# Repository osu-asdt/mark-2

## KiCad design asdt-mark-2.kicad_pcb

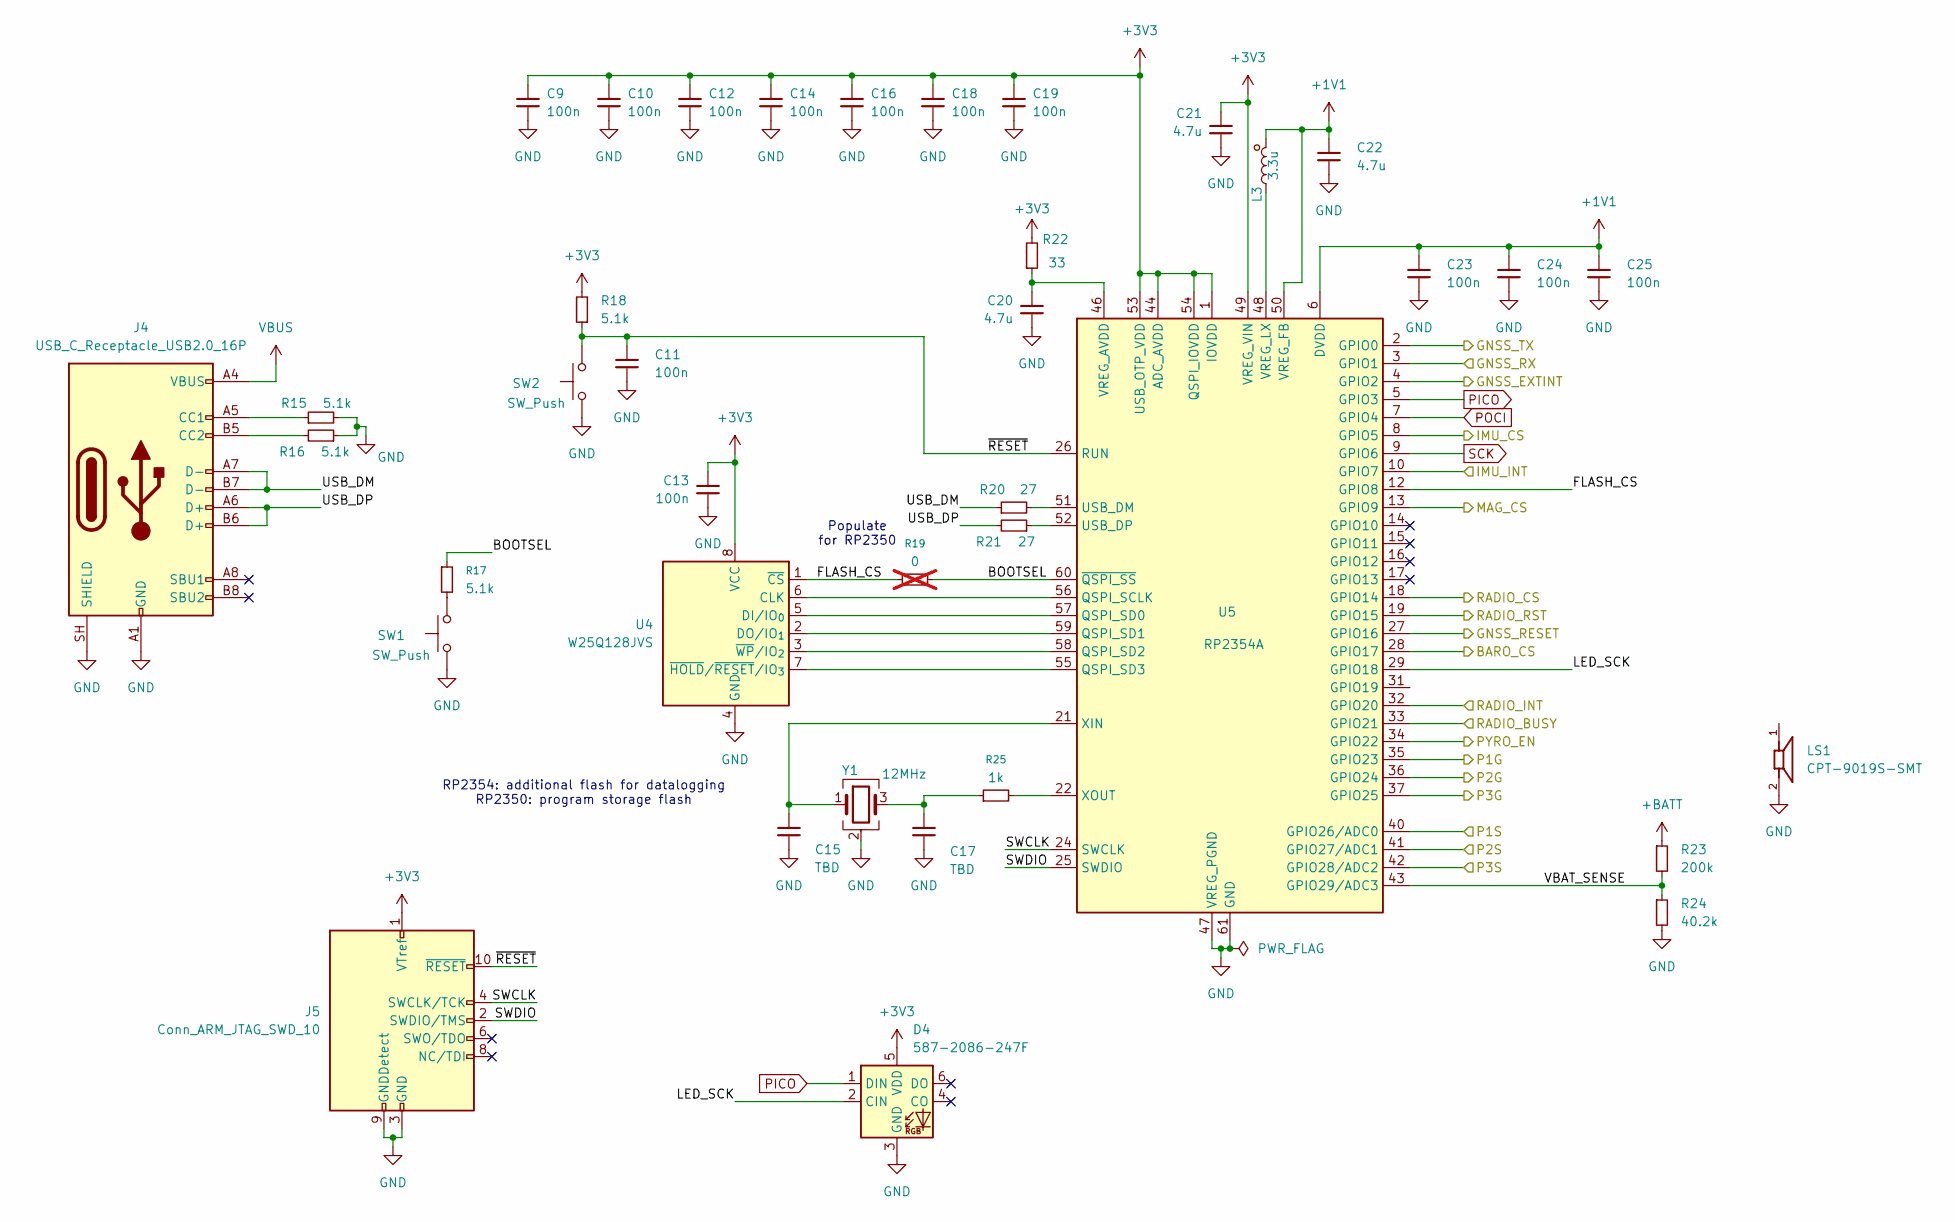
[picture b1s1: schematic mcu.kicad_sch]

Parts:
C9, C10, C12, C13, C14, C16, C18, C19: 100n; C_0201_0603Metric
C11: 100n; C_0201_0603Metric; Voltage 6.3V
C15, C17: TBD; C_0201_0603Metric
C20: 4.7u; C_0402_1005Metric
C21, C22: 4.7u; C_0402_1005Metric; Voltage 10V
C23, C24, C25: 100n; C_0201_0603Metric; Voltage 16V
D4: 587-2086-247F; LED-587-2086-247F-3228
J4: USB_C_Receptacle_USB2.0_16P; USB_C_Receptacle_GCT_USB4105-xx-A_16P_TopMnt_Horizontal
J5: Conn_ARM_JTAG_SWD_10; PinHeader_2x05_P1.27mm_Vertical_SMD
L3: 3.3u; L_0806_2016Metric
LS1: CPT-9019S-SMT; CUI_CPT-9019S-SMT; MPN CPT-9019S-SMT-TR
R15, R16, R17, R18: 5.1k; R_0201_0603Metric
R19: 0; R_0201_0603Metric; not fitted
R20, R21: 27; R_0201_0603Metric
R22: 33; R_0201_0603Metric
R23: 200k; R_0201_0603Metric
R24: 40.2k; R_0201_0603Metric
R25: 1k; R_0201_0603Metric
SW1, SW2: SW_Push; SW_SPST_PTS810
U4: W25Q128JVS; SOIC-8_5.3x5.3mm_P1.27mm
U5: RP2354A; QFN-60-1EP_7x7mm_P0.4mm_EP3.4x3.4mm
Y1: 12MHz; Crystal_SMD_Abracon_ABM8G-4Pin_3.2x2.5mm

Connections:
+1V1: C22.1, C23.1, C24.1, C25.1, L3.1, U5.6 (DVDD), U5.23 (DVDD), U5.39 (DVDD), U5.50 (VREG_FB)
+3V3: C9.1, C10.1, C12.1, C13.1, C14.1, C16.1, C18.1, C19.1, C21.1, D4.5 (VDD), J5.1 (VTref), R18.2, R22.2, U4.8 (VCC), U5.1 (IOVDD), U5.11 (IOVDD), U5.20 (IOVDD), U5.30 (IOVDD), U5.38 (IOVDD), U5.44 (ADC_AVDD), U5.45 (IOVDD), U5.49 (VREG_VIN), U5.53 (USB_OTP_VDD), U5.54 (QSPI_IOVDD); also elsewhere on the board
+BATT: R23.1; also elsewhere on the board
/MCU/BARO_CS: U5.28 (GPIO17)
/MCU/BOOTSEL: R17.1, R19.2, U5.60 (~QSPI_SS)
/MCU/FLASH_CS: R19.1, U4.1 (~CS), U5.12 (GPIO8)
/MCU/GNSS_EXTINT: U5.4 (GPIO2); also elsewhere on the board
/MCU/GNSS_RESET: U5.27 (GPIO16); also elsewhere on the board
/MCU/GNSS_RX: U5.3 (GPIO1); also elsewhere on the board
/MCU/GNSS_TX: U5.2 (GPIO0); also elsewhere on the board
/MCU/IMU_CS: U5.8 (GPIO5); also elsewhere on the board
/MCU/IMU_INT: U5.10 (GPIO7); also elsewhere on the board
/MCU/LED_SCK: D4.2 (CIN), U5.29 (GPIO18)
/MCU/MAG_CS: U5.13 (GPIO9); also elsewhere on the board
/MCU/P1G: U5.35 (GPIO23); also elsewhere on the board
/MCU/P1S: U5.40 (GPIO26/ADC0); also elsewhere on the board
/MCU/P2G: U5.36 (GPIO24); also elsewhere on the board
/MCU/P2S: U5.41 (GPIO27/ADC1); also elsewhere on the board
/MCU/P3G: U5.37 (GPIO25); also elsewhere on the board
/MCU/P3S: U5.42 (GPIO28/ADC2); also elsewhere on the board
/MCU/PYRO_EN: U5.34 (GPIO22); also elsewhere on the board
/MCU/RADIO_BUSY: U5.33 (GPIO21); also elsewhere on the board
/MCU/RADIO_CS: U5.18 (GPIO14); also elsewhere on the board
/MCU/RADIO_INT: U5.32 (GPIO20); also elsewhere on the board
/MCU/RADIO_RST: U5.19 (GPIO15); also elsewhere on the board
/MCU/SWCLK: J5.4 (SWCLK/TCK), U5.24 (SWCLK)
/MCU/SWDIO: J5.2 (SWDIO/TMS), U5.25 (SWDIO)
/MCU/USB_DM: J4.A7 (D-), J4.B7 (D-), R20.1
/MCU/USB_DP: J4.A6 (D+), J4.B6 (D+), R21.2
/MCU/VBAT_SENSE: R23.2, R24.1, U5.43 (GPIO29/ADC3)
/MCU/~RESET: C11.1, J5.10 (~RESET), R18.1, SW2.2, U5.26 (RUN)
GND: C9.2, C10.2, C11.2, C12.2, C13.2, C14.2, C15.2, C16.2, C17.2, C18.2, C19.2, C20.2, C21.2, C22.2, C23.2, C24.2, C25.2, D4.3 (GND), J4.A1 (GND), J4.A12 (GND), J4.B1 (GND), J4.B12 (GND), J4.SH (SHIELD), J5.3 (GND), J5.5 (GND), J5.9 (GNDDetect), R15.2, R16.1, R24.2, SW1.1, SW2.1, U4.4 (GND), U5.47 (VREG_PGND), U5.61 (GND), Y1.2 (G), Y1.4 (G); also elsewhere on the board
unnamed: C17.1, R25.1, Y1.3
unnamed: J4.A5 (CC1), R15.1
unnamed: J4.B5 (CC2), R16.2
unnamed: R17.2, SW1.2
unnamed: U4.6 (CLK), U5.56 (QSPI_SCLK)
unnamed: U4.5 (DI/IO_{0}), U5.57 (QSPI_SD0)
unnamed: U4.2 (DO/IO_{1}), U5.59 (QSPI_SD1)
unnamed: U4.7 (~HOLD/~RESET/IO_{3}), U5.55 (QSPI_SD3)
unnamed: U4.3 (~WP/IO_{2}), U5.58 (QSPI_SD2)
unnamed: R20.2, U5.51 (USB_DM)
unnamed: R21.1, U5.52 (USB_DP)
unnamed: C20.1, R22.1, U5.46 (VREG_AVDD)
unnamed: L3.2, U5.48 (VREG_LX)
unnamed: C15.1, U5.21 (XIN), Y1.1
unnamed: R25.2, U5.22 (XOUT)
PICO: D4.1 (DIN), U5.5 (GPIO3); also elsewhere on the board
POCI: U5.7 (GPIO4); also elsewhere on the board
SCK: U5.9 (GPIO6); also elsewhere on the board
VBUS: J4.A4 (VBUS), J4.A9 (VBUS), J4.B4 (VBUS), J4.B9 (VBUS); also elsewhere on the board

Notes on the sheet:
Populate for RP2350
RP2354: additional flash for datalogging RP2350: program storage flash

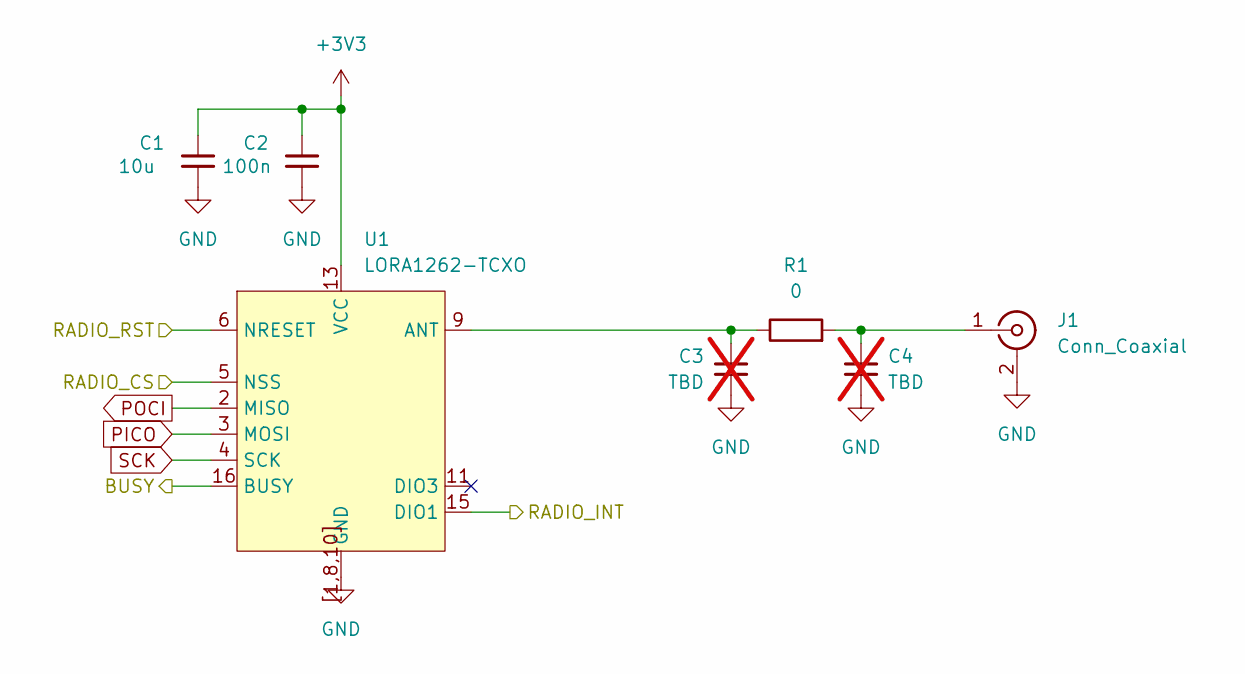
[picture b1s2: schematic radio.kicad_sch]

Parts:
C1: 10u; R_0603_1608Metric
C2: 100n; C_0201_0603Metric
C3, C4: TBD; C_0201_0603Metric; not fitted
J1: Conn_Coaxial; SMA_Samtec_SMA-J-P-H-ST-EM1_EdgeMount
R1: 0; R_0201_0603Metric
U1: LORA1262-TCXO; NiceRF-LORA126x

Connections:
+3V3: C1.1, C2.1, U1.13 (VCC); also elsewhere on the board
/MCU/RADIO_BUSY: U1.16 (BUSY); also elsewhere on the board
/MCU/RADIO_CS: U1.5 (NSS); also elsewhere on the board
/MCU/RADIO_INT: U1.15 (DIO1); also elsewhere on the board
/MCU/RADIO_RST: U1.6 (NRESET); also elsewhere on the board
GND: C1.2, C2.2, C3.2, C4.2, J1.2 (Ext), U1.[1,8,10] (GND); also elsewhere on the board
unnamed: C4.1, J1.1 (In), R1.2
unnamed: C3.1, R1.1, U1.9 (ANT)
PICO: U1.3 (MOSI); also elsewhere on the board
POCI: U1.2 (MISO); also elsewhere on the board
SCK: U1.4 (SCK); also elsewhere on the board

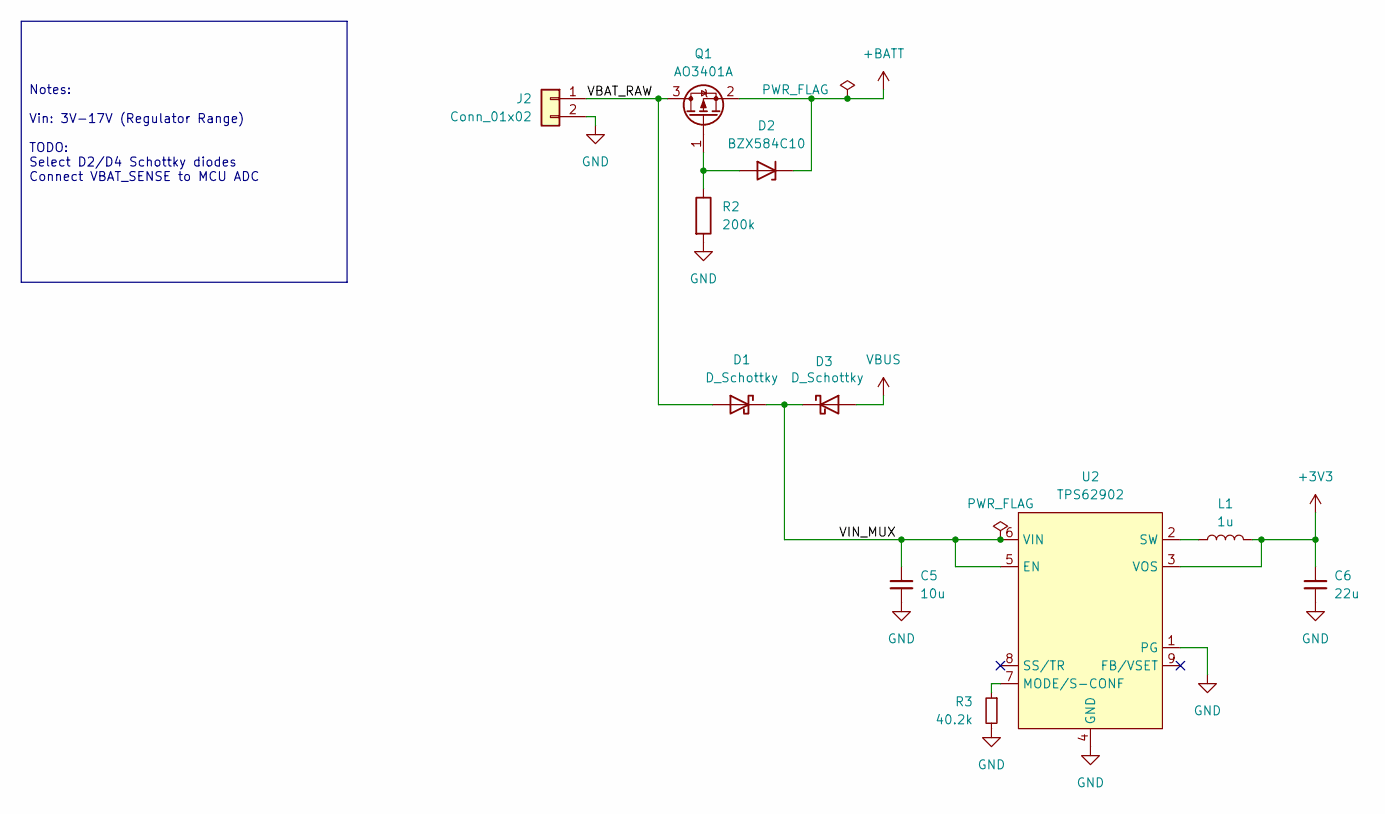
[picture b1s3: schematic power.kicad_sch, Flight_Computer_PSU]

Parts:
C5: 10u; R_0603_1608Metric
C6: 22u; R_0402_1005Metric
D1, D3: D_Schottky; D_SOD-123
D2: BZX584C10; D_SOD-523; LCSC Part# C22395577
J2: Conn_01x02; TerminalBlock_Xinya_XY308-2.54-2P_1x02_P2.54mm_Horizontal
L1: 1u; L_1008_2520Metric
Q1: AO3401A; SOT-23
R2: 200k; R_0201_0603Metric
R3: 40.2k; R_0201_0603Metric
U2: TPS62902; Texas_RPJ0009A_VQFN-HR-9_1.5x2mm_P0.5mm

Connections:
+3V3: C6.1, L1.2, U2.3 (VOS); also elsewhere on the board
+BATT: D2.1 (K), Q1.2 (S); also elsewhere on the board
/Power/VBAT_RAW: D1.2 (A), J2.1, Q1.3 (D)
/Power/VIN_MUX: C5.1, D1.1 (K), D3.1 (K), U2.5 (EN), U2.6 (VIN)
GND: C5.2, C6.2, J2.2, R2.2, R3.2, U2.1 (PG), U2.4 (GND); also elsewhere on the board
unnamed: D2.2 (A), Q1.1 (G), R2.1
unnamed: R3.1, U2.7 (MODE/S-CONF)
unnamed: L1.1, U2.2 (SW)
VBUS: D3.2 (A); also elsewhere on the board

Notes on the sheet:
Notes: Vin: 3V-17V (Regulator Range) TODO: Select D2/D4 Schottky diodes Connect VBAT_SENSE to MCU ADC

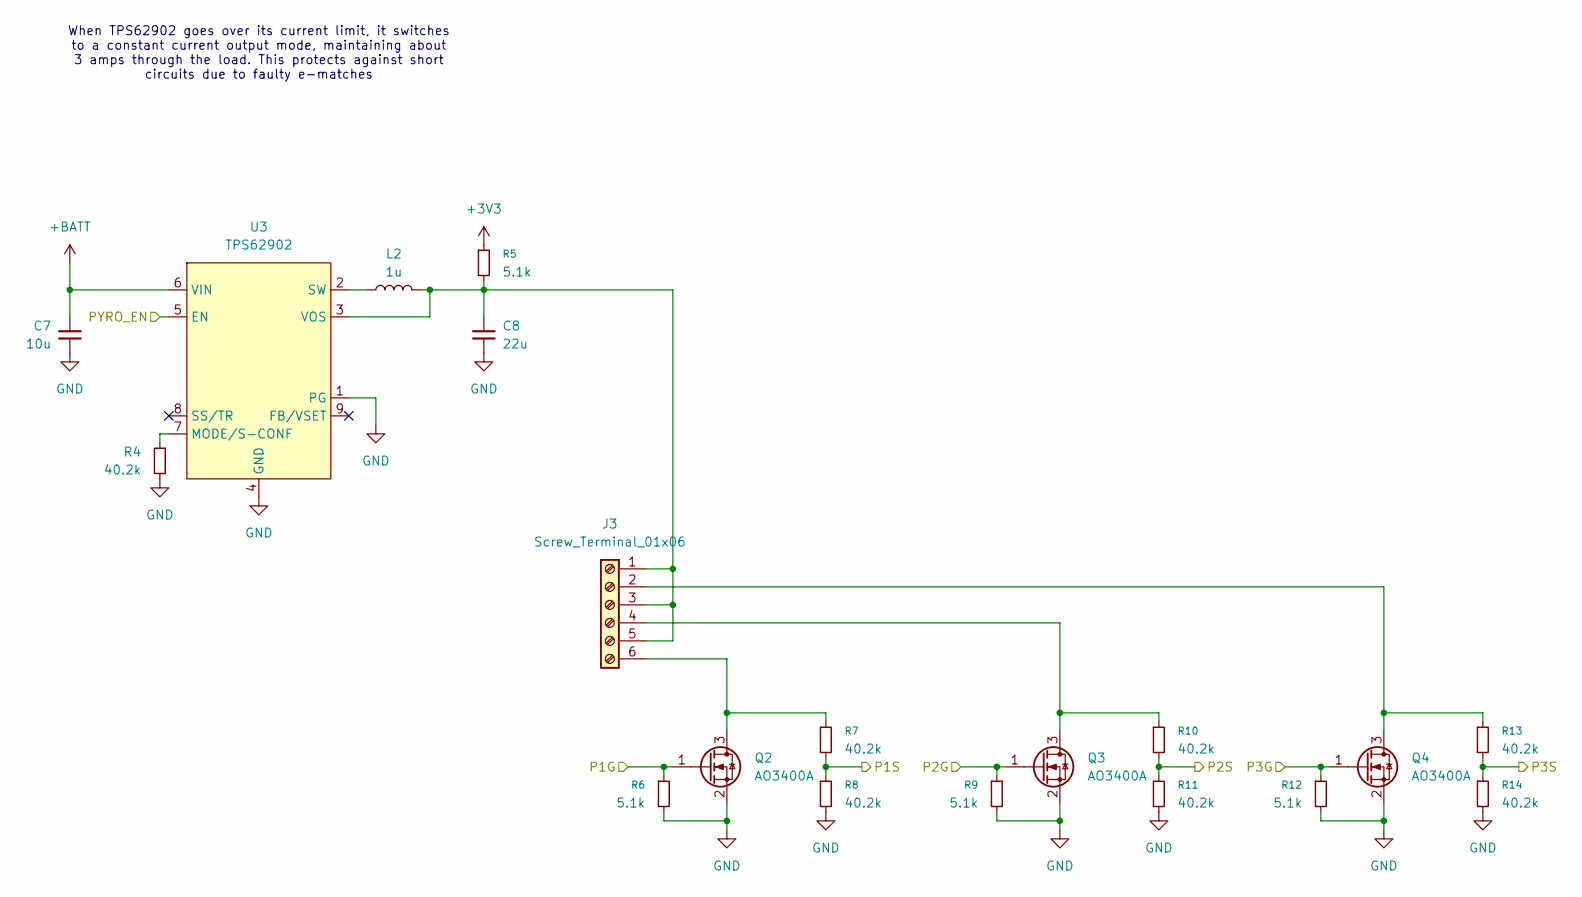
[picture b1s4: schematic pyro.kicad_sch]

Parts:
C7: 10u; R_0603_1608Metric
C8: 22u; R_0402_1005Metric
J3: Screw_Terminal_01x06; TerminalBlock_Xinya_XY308-2.54-6P_1x06_P2.54mm_Horizontal
L2: 1u; L_1008_2520Metric
Q2, Q3, Q4: AO3400A; SOT-23
R4, R7, R8, R10, R11, R13, R14: 40.2k; R_0201_0603Metric
R5, R6, R9, R12: 5.1k; R_0201_0603Metric
U3: TPS62902; Texas_RPJ0009A_VQFN-HR-9_1.5x2mm_P0.5mm

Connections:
+3V3: R5.1; also elsewhere on the board
+BATT: C7.1, U3.6 (VIN); also elsewhere on the board
/MCU/P1G: Q2.1 (G), R6.1; also elsewhere on the board
/MCU/P1S: R7.2, R8.1; also elsewhere on the board
/MCU/P2G: Q3.1 (G), R9.1; also elsewhere on the board
/MCU/P2S: R10.2, R11.1; also elsewhere on the board
/MCU/P3G: Q4.1 (G), R12.1; also elsewhere on the board
/MCU/P3S: R13.2, R14.1; also elsewhere on the board
/MCU/PYRO_EN: U3.5 (EN); also elsewhere on the board
GND: C7.2, C8.2, Q2.2 (S), Q3.2 (S), Q4.2 (S), R4.2, R6.2, R8.2, R9.2, R11.2, R12.2, R14.2, U3.1 (PG), U3.4 (GND); also elsewhere on the board
unnamed: C8.1, J3.1, J3.3, J3.5, L2.2, R5.2, U3.3 (VOS)
unnamed: J3.2, Q4.3 (D), R13.1
unnamed: J3.4, Q3.3 (D), R10.1
unnamed: J3.6, Q2.3 (D), R7.1
unnamed: R4.1, U3.7 (MODE/S-CONF)
unnamed: L2.1, U3.2 (SW)

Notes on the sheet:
When TPS62902 goes over its current limit, it switches to a constant current output mode, maintaining about 3 amps through the load. This protects against short circuits due to faulty e-matches

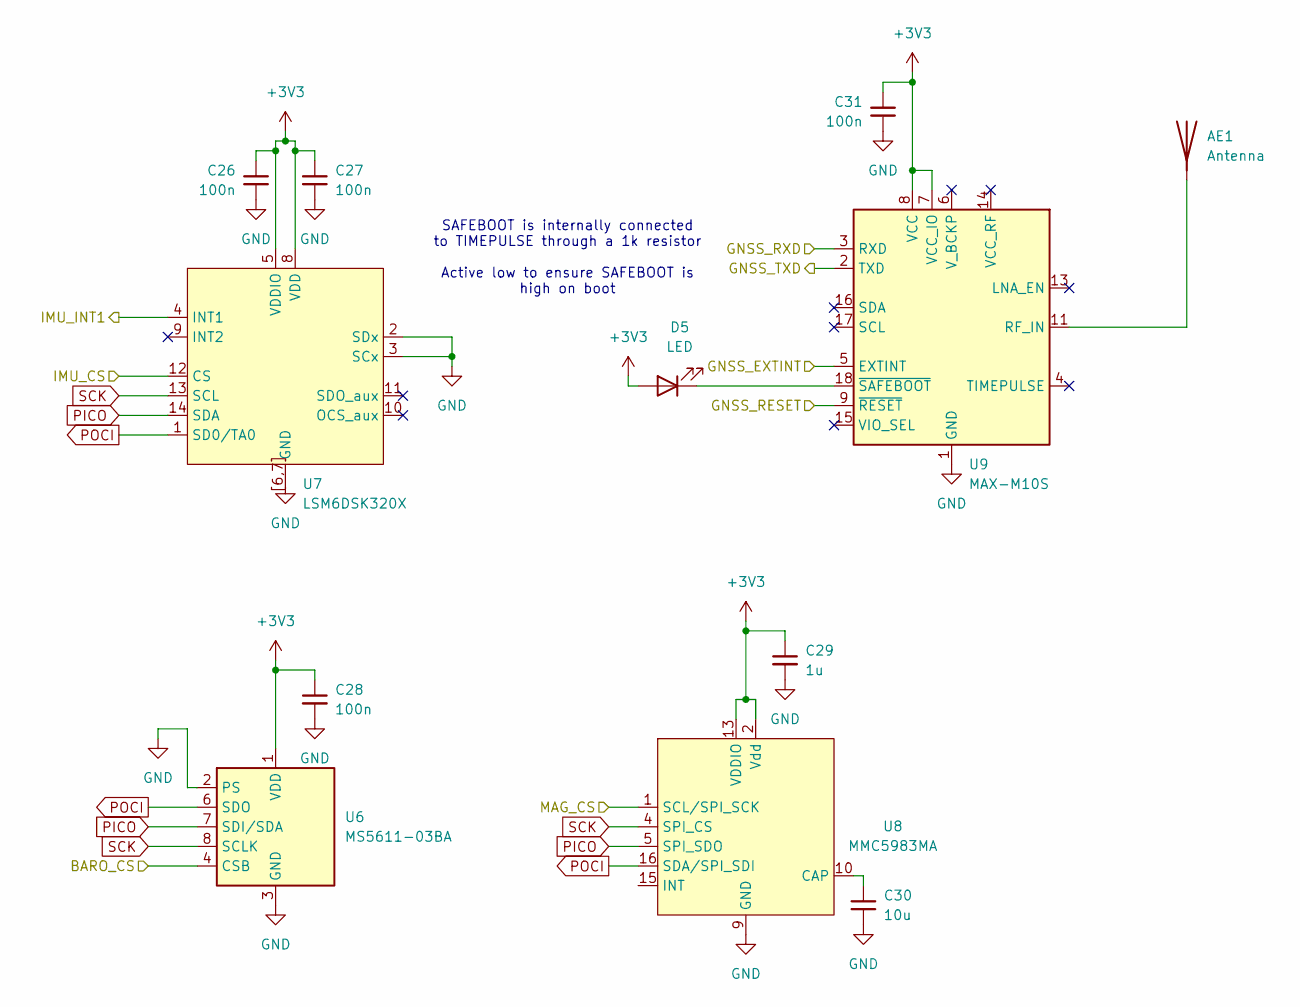
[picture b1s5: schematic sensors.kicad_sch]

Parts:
AE1: Antenna
C26, C27, C31: 100n; C_0201_0603Metric
C28: 100n; C_0201_0603Metric; LCSC C1525
C29: 1u; C_0201_0603Metric; LCSC C1525
C30: 10u; R_0603_1608Metric
D5: LED; D_0603_1608Metric
U6: MS5611-03BA; LGA-8_3x5mm_P1.25mm; LCSC C97627
U7: LSM6DSK320X; LGA-14_3x2.5mm_P0.5mm_LayoutBorder3x4y
U8: MMC5983MA; LGA-16_3x3mm_P0.5mm
U9: MAX-M10S; ublox_MAX

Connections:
+3V3: C26.2, C27.2, C28.1, C29.1, C31.1, D5.2 (A), U6.1 (VDD), U7.5 (VDDIO), U7.8 (VDD), U8.2 (Vdd), U8.13 (VDDIO), U9.7 (VCC_IO), U9.8 (VCC); also elsewhere on the board
/MCU/GNSS_EXTINT: U9.5 (EXTINT); also elsewhere on the board
/MCU/GNSS_RESET: U9.9 (~RESET); also elsewhere on the board
/MCU/GNSS_RX: U9.2 (TXD); also elsewhere on the board
/MCU/GNSS_TX: U9.3 (RXD); also elsewhere on the board
/MCU/IMU_CS: U7.12 (CS); also elsewhere on the board
/MCU/IMU_INT: U7.4 (INT1); also elsewhere on the board
/MCU/MAG_CS: U8.1 (SCL/SPI_SCK); also elsewhere on the board
/Sensors/BARO_CS: U6.4 (CSB), U6.5 (CSB)
GND: C26.1, C27.1, C28.2, C29.2, C30.2, C31.2, U6.2 (PS), U6.3 (GND), U7.2 (SDx), U7.3 (SCx), U7.6 (GND), U7.7 (GND), U7.[6,7] (GND), U8.9 (GND), U8.11 (GND), U9.1 (GND), U9.10 (GND), U9.12 (GND); also elsewhere on the board
unnamed: AE1.1, U9.11 (RF_IN)
unnamed: D5.1 (K), U9.18 (~SAFEBOOT)
unnamed: C30.1, U8.10 (CAP)
PICO: U6.7 (SDI/SDA), U7.14 (SDA), U8.5 (SPI_SDO); also elsewhere on the board
POCI: U6.6 (SDO), U7.1 (SD0/TA0), U8.16 (SDA/SPI_SDI); also elsewhere on the board
SCK: U6.8 (SCLK), U7.13 (SCL), U8.4 (SPI_CS); also elsewhere on the board

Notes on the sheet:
SAFEBOOT is internally connected to TIMEPULSE through a 1k resistor Active low to ensure SAFEBOOT is high on boot

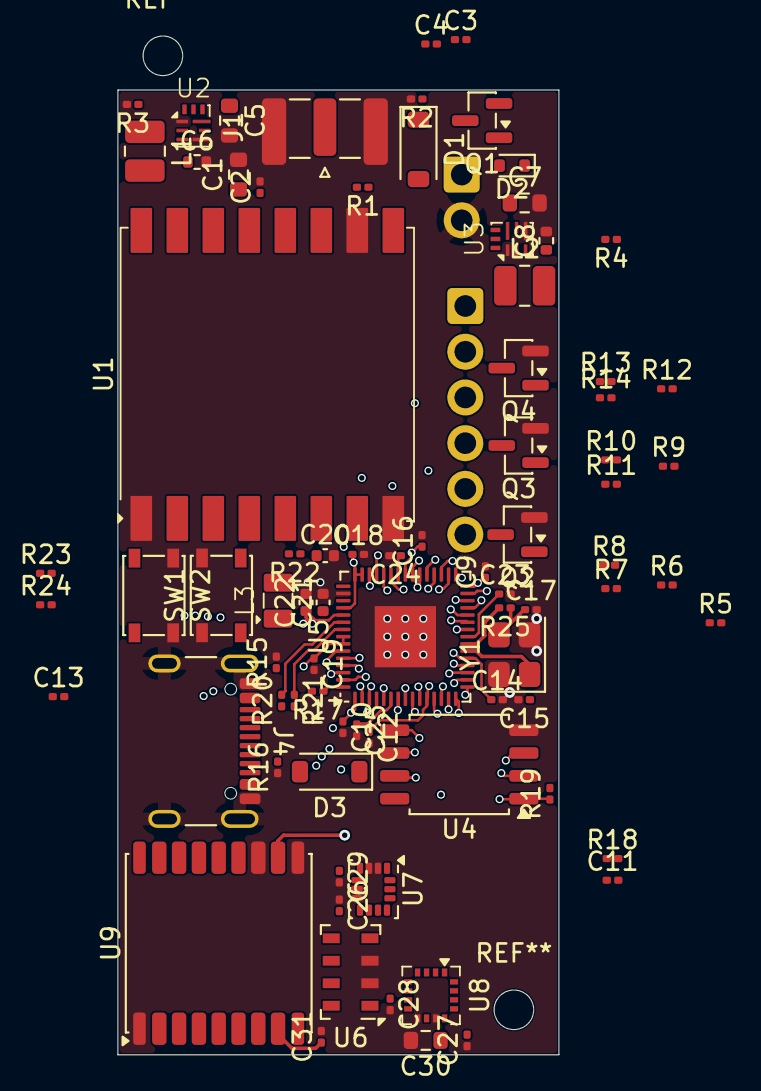
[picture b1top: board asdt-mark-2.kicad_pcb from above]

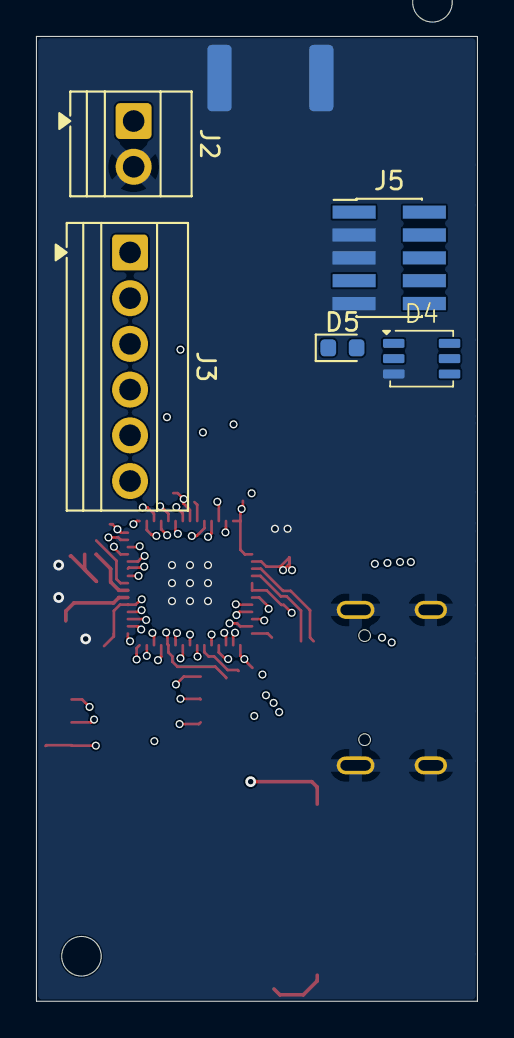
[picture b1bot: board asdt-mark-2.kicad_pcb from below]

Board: 4 copper layers, 24.5 x 53.6 mm, 85 parts (5 on the bottom side), 66 nets.
